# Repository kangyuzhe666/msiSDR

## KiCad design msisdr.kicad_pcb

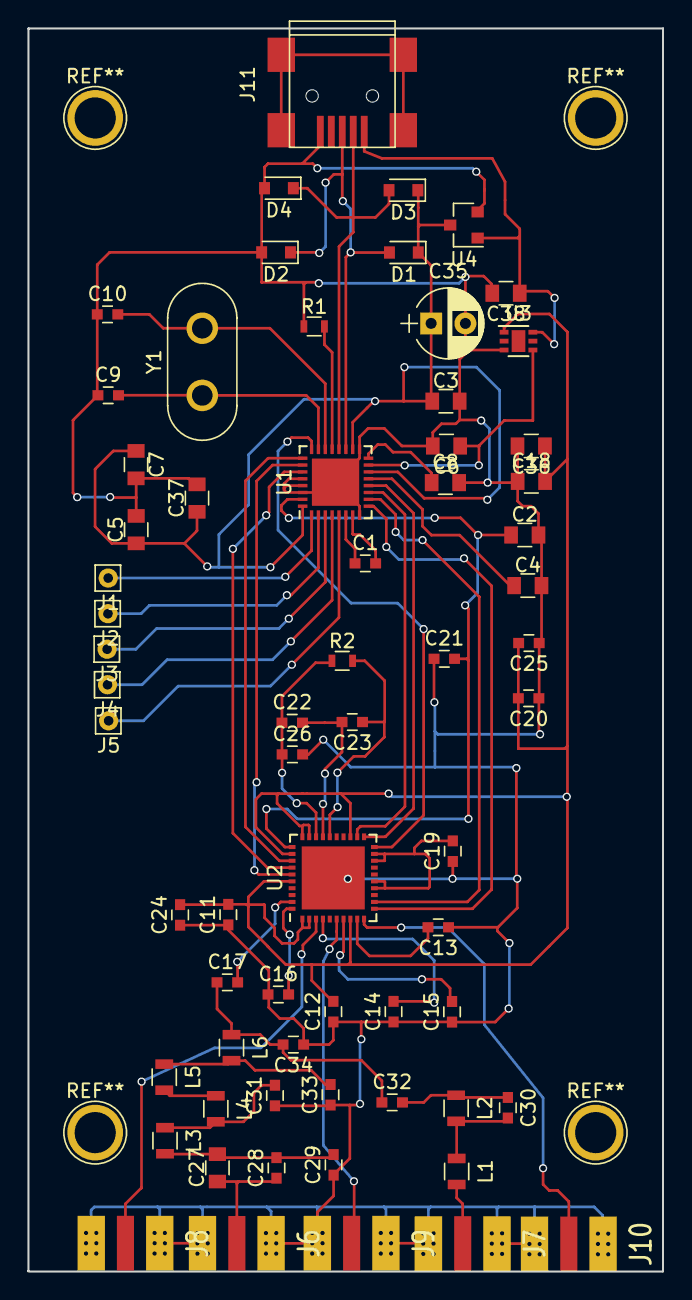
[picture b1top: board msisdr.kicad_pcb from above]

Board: 2 copper layers, 46.3 x 90.7 mm, 66 parts (0 on the bottom side), 49 nets.

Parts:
C1, C11, C12, C13, C14, C15, C19, C20, C21, C24, C25, C26: 10nF; C_0603
C2, C3, C4, C5, C7, C36, C37, C38: 10uF; C_0805
C6, C8, C18: 1uF; C_0805
C9, C10: 18pF; C_0603
C16, C17: 100nF; C_0603
C22, C23: 6800pF; C_0603
C27: 470nF; C_0805
C28: 1nF; C_0603
C29, C34: 56pF; C_0603
C30: 3.9pF; C_0603
C31, C33: 160pF; C_0603
C32: 39pF; C_0603
C35: 100uF; CP_Radial_D5.0mm_P2.50mm
D1, D2, D3, D4: D; D_0805
J1: VCC_GPIO; Pin_d0.7mm_L6.5mm_W1.8mm_FlatFork
J2: GPIO0; Pin_d0.7mm_L6.5mm_W1.8mm_FlatFork
J3: GPIO1; Pin_d0.7mm_L6.5mm_W1.8mm_FlatFork
J4: GPIO2; Pin_d0.7mm_L6.5mm_W1.8mm_FlatFork
J5: GPIO3; Pin_d0.7mm_L6.5mm_W1.8mm_FlatFork
J6: SMA_0_30MHZ; SMA_OPL_EM
J7: SMA_30_60MHZ; SMA_OPL_EM
J8: SMA_VHF2; SMA_OPL_EMPTYHEAD
J9: SMA_UHF; SMA_OPL_EMPTYHEAD
J10: SMA_VHF1; SMA_OPL_EMPTYHEAD
J11: USB_OTG; USB_Mini-B
L1: 220nH; L_0805
L2, L3, L6: 330nH; L_0805
L4: 270nH; L_0805
L5: 150nH; L_0805
R1: 510R; R_0603
R2: 390R; R_0603
U1: msi2500; QFN-32-1EP_5x5mm_Pitch0.5mm
U2: msi001; QFN-40-1EP_6x6mm_Pitch0.5mm
U3: LP5900SDX-2.8; DFN-6-1EP_2x2mm_Pitch0.65mm
U4: AP7313-30SAG; SOT-23
Y1: 24MHz; Crystal_HC50_Vertical

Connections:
GND: C2.2, C3.2, C4.2, C5.2, C6.2, C7.2, C8.2, C9.1, C10.1, C11.1, C12.1, C13.1, C14.1, C15.1, C16.1, C18.1, C19.1, C20.1, C21.1, C24.1, C25.1, C26.2, C29.1, C31.1, C33.1, C34.1, C35.2, C36.2, C37.2, C38.2, D2.2, D4.2, J6.2, J6.3, J7.2, J7.3, J8.2, J8.3, J9.2, J9.3, J10.2, J10.3, J11.5, R1.1, U1.8, U1.17, U1.28, U1.29, U1.30, U1.33, U2.41, U3.3, U4.2
HFPORT: C17.1, C32.1, C34.2, L6.1
I_IN_N: U1.10, U2.12
I_IN_P: U1.9, U2.11
unnamed: C1.1, U1.6
unnamed: C1.2, U1.7
unnamed: C4.1, U1.13
unnamed: C8.1, U1.16
unnamed: C9.2, U1.23, Y1.1
unnamed: C10.2, U1.22, Y1.2
unnamed: C13.2, U2.9
unnamed: C14.2, U2.4
unnamed: C15.2, U2.7
unnamed: C16.2, U2.40
unnamed: C17.2, U2.39
unnamed: C19.2, U2.14, U2.15, U2.18, U2.19
unnamed: C22.1, C26.1, R2.1, U2.28
unnamed: C22.2, C23.2, U2.27
unnamed: C23.1, R2.2, U2.26
unnamed: C27.1, C28.1, J6.1
unnamed: C27.2, C28.2, C29.2, L3.2
unnamed: C30.1, C32.2, L2.1
unnamed: C30.2, L1.1, L2.2
unnamed: C31.2, L3.1, L4.2
unnamed: C33.2, L5.1, L6.2
unnamed: C38.1, J11.1, U3.6, U4.1
unnamed: J1.1, U1.1
unnamed: J2.1, U1.2
unnamed: J3.1, U1.3
unnamed: J4.1, U1.4
unnamed: J5.1, U1.5
unnamed: J7.1, L1.2
unnamed: L4.1, L5.2
unnamed: R1.2, U1.21
Q_IN_N: U1.12, U2.21
Q_IN_P: U1.11, U2.22
REFCLK: U1.24, U2.20
SPI_CLK: U1.27, U2.34
SPI_DATA: U1.26, U2.35
SPI_LAT: U1.25, U2.33
UHF_400_1000MHZ: J9.1, U2.6
USB_DM: D3.2, D4.1, J11.2, U1.20
USB_DP: D1.2, D2.1, J11.3, U1.19
V18-SYNTH: C6.1, U1.15, U3.4
VDDI: C2.1, C21.2, U1.31, U2.31
VDIG: C3.1, C5.1, C7.1, C35.1, C37.1, D1.1, D3.1, U1.14, U1.18, U1.32, U4.3
VHF_50_120MHZ: J10.1, U2.10
VHF_120_250MHZ: J8.1, U2.3
VRF: C11.2, C12.2, C18.2, C20.2, C24.2, C25.2, C36.1, U2.1, U2.2, U2.8, U2.23, U2.29, U2.30, U2.32, U2.36, U3.1

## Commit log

2019-02-25 fix ldo ap7313 bug
